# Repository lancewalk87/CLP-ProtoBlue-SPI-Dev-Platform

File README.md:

# ProtoBlue SPI Development Platform

### Project Structure:
* [**docs**](https://github.com/lancewalk87/CLP-ProtoBlue-SPI-Dev-Platform/tree/master/docs): Project Documentation.
* [**Drivers**](https://github.com/lancewalk87/CLP-ProtoBlue-SPI-Dev-Platform/tree/master/Drivers): Device System Software.
* [**Models**](https://github.com/lancewalk87/CLP-ProtoBlue-SPI-Dev-Platform/tree/master/Models): Device Hardware.
* [**PCBs**](https://github.com/lancewalk87/CLP-ProtoBlue-SPI-Dev-Platform/tree/master/PCBs): Device Circuits.
* [**Schematics**](https://github.com/lancewalk87/CLP-ProtoBlue-SPI-Dev-Platform/tree/master/Schematics): Device Schematics.  
* [**Client_Portals**](https://github.com/lancewalk87/CLP-ProtoBlue-SPI-Dev-Platform/tree/master/Client_Portals): Client Portals: Browser, Android, iOS, Windows, macOSX.    

General - General Purpose Digital Dev/Debug Platform
----------------------------------------------------
#### The ProtoBlue is capable of interfacing with any USB or Wifi/BlueTooth Enabled device, this allows for dynamic and convenient production testing via it's numerous onboard GPIO configurations and peripheral I/0. Capable of transceiving data of up to 72.2Mbps, the ESP8266EX Wireless chip offers a standard Wifi enabled (implementing TCP/IP as well as WLAN MAC protocols) baseband, clocked at 2.4GHz (Rx/Tx) making connection to the debugger ubiquitious amoungest all modern devices. In addition to efficent onboard power management (See Schematic Pg.3 - System Power Diagram), the device is capable of functioning independent of a sustained power supply and has an onboard 3.7v 560mAH LIPO battery complete with Temp Sense for safe and efficent battery rechargablity when the device is plugged in.

#### The Client Portal, available on iOS, Android, macOS, and Windows, acts as a fully functional MCU SDK, and Debug IDE. Allowing for both standard Assembly C/C++ binaries, as well as the Ardunio IDE (Objective-C) equivalent. The versataile operating system, and accessible GPIO makes the ProtoBlue the most reliable and efficent Debug platform available for any and all MCUs. In addition to the convinent ability to fix code reliably, the ProtoBlue Client Portal allows you to view (either post or pre debug session) individual bit states at any given device I/O Port, ADC, EEPROM, Interrupt, Clock, or SPI, you can investiga te each of your device's operations at a binary level.  

#### Given an additional 16GB of Non-Volataile NAND Flash Memory, you can store, edit, and review existing debug sessions in order to illustrate a more clear and foundational understanding of the intricate circuit you are trying to work the kinks out of. This storage also allows you to keep your projects together in a virtual space that is always connected to the hardware capable of performing real-world tests, without the tedious and redundant act of building new testing modules everytime you want to start or resume a different project.  

#### The ProtoBlue, as mentioned above, is capable of performing debug sessions without an additional MCU because the Primary MCU is not integral to the device's Power Management, USB, Wireless, or NAND Flash Memory functionality. Meaning the massive WS2812Bx48 Individually Addressable RGB LED Arrary can be used for a vast number of things ranging from validating data manipulative software (i.e. bitwise tests, timer tests, ttl comparisons), to the implementation of algorithms (i.e. Recursive, Backtracking, Divide/Conquer, Randomizing), to the optimization of the Device RunCycle (i.e. Multithreading, Preprocessing, Error/Exception Handling), to the efficent delegation of finite System resources (SRAM Deallocation/Allocation, Encryption/Overwriting of superfluous data, Conserving Energy by Shifting Power Modes). In conjunction to the LED Array, there are also Buttons connected to the Primary MCU, allowing for variable tactile user inputs.

### Architecture Support & Device Compatibility
#### The debug platform is capable of connecting to any device whose controller has ISP capabilities, this will include the vast majority of main line MCUs; including that of PIC series, and AVR series Microcontrollers. Depending on the MCU FlashROM made accessible to the ProtoBlue, the device will be capable of interfacing with the registers to grant access to the complex and detailed debuging tools defined above.

Debugging & Programming Targets
-------------------------------
### Programming Your Target
#### Make the proper ICSP connections to your target device's SPI (VCC, GND, MOSI, MISO, SCK, RESET), the ProtoBlue will interpret the target's signature and attempt to evaluate any preexisting EEPROM data. After configuring any neccesary ICSP variables, and cacheing a record of the debug session to it's NAND Flash Storage for later evaluation, the ProtoBlue will begin programming your target with the specefied code. You can review active or past debug sessions in the "debug" view of whatever client device you're using to carry out your tests (See Project Overview for full details on the Native Client environments).

### Debugging Your Target
#### Once your target has been uploaded with a binary, and is executing the instruction set accordingly you will be able to begin your debug session. After the ProtoBlue has completed programming over ISP, the user portal will give the option to begin a serial debug session. If you wish to proceed in debugging, select continue, and set the debug session settings when the window to do so presents itself.

#### These presets allows you to define the session's level of detail, certain types of debug sessions don't require massive amounts of detail, while others do, these presets allow you to determine that accuracy before the the initialization of the testing process. Once the session has been defined, the Protoblue will begin monitoring the target in a similar fashion to a typical JTag device.

#### When you have observed the behavior you either expected or did not expect, you can terminate the debug session and save it to your project cache.

### Bootloading Your Target
#### The onboard NANDFlash has allocated stoarge space to industry standard Bootloaders, the most prominent of which being the Ardunio Bootloader for AVR series Microcontrollers. For this example we will use this bootloader to demonstrate how to successfully bootload a target, though please note, you can upload any bootloader to your ProtoBlue and be successful in uploading it to a target.

#### To bootload a target you must connect the ProtoBlue via ISCP to your target's ICSP.

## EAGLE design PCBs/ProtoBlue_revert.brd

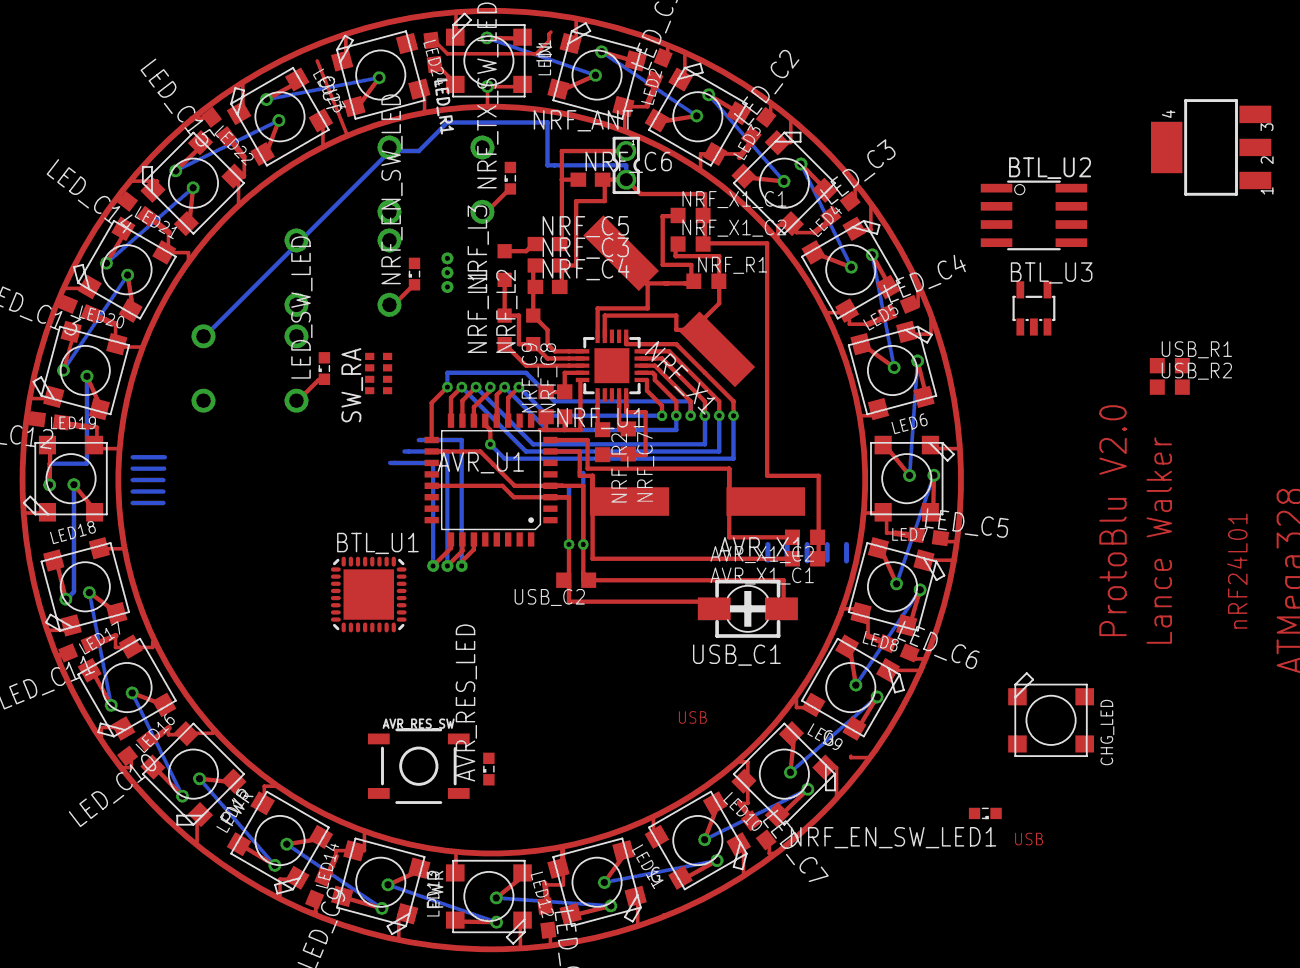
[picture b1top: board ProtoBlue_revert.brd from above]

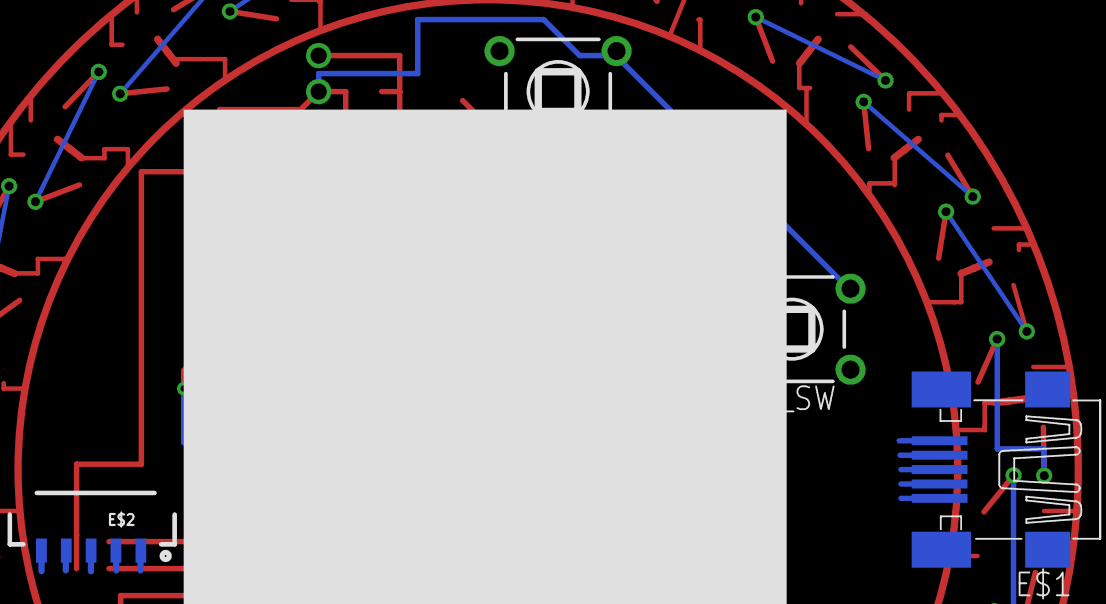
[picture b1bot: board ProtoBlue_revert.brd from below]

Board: 2 copper layers, 82 parts (5 on the bottom side), 3 nets.

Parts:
AVR_RES_LED: LED_SML0603
AVR_RES_SW: TACTILE_SWITCH_SMD_5.2MM
AVR_U1: 328AU; VQFP32
AVR_X1: 16MHz; CSM-7X-DU
AVR_X1_C1, AVR_X1_C2: 22pF; C0603K
BTL_IC1: MC33269ST-5.0T3; SOT223
BTL_U1: ATMEGA8U2-MU; QFN32
BTL_U2: SO08
BTL_U3: LP2985-33DBVR; SOT23-DBV
CHG_LED: WS2812B5050; WS2812B-NARROW
E$1: USB; 32005-400
E$2: BATT_IN; 1X05_1MM_RA
LED1, LED2, LED3, LED4, LED5, LED6, LED7, LED8, LED9, LED10, LED11, LED12, LED13, LED14, LED15, LED16, LED17, LED18, LED19, LED20, LED21, LED22, LED23, LED24: WS2812B5050; WS2812B-NARROW
LED_C1, LED_C2, LED_C3, LED_C4, LED_C5, LED_C6, LED_C7, LED_C8, LED_C9, LED_C10, LED_C11, LED_C12, LED_C13, LED_C14, LED_C15: 100nF; C0603
LED_R1: 0603-NO
LED_SW: TL1105T
LED_SW_LED: LED_SML0603
NRF_ANT: 332-02
NRF_C3: 2.2nF; C0603
NRF_C4: 4.7pF; C0603
NRF_C5: 1.5pF; C0603
NRF_C6: 1pF; C0603
NRF_C7: 33nF; C0603K
NRF_C8: 1nF; C0603K
NRF_C9: 10nF; C0603K
NRF_EN_SW: TL1105T
NRF_EN_SW_LED, NRF_EN_SW_LED1: LED_SML0603
NRF_L1: 8.2nH; L2012C
NRF_L2: 3.9nH; L2012C
NRF_L3: 2.7nH; L2012C
NRF_R1: 1M; C0603K
NRF_R2: 22K; C0603K
NRF_TX_SW: TL1105T
NRF_TX_SW_LED: LED_SML0603
NRF_U1: nRF24L01; QFN20
NRF_X1: 16MHz; CSM-7X-DU
NRF_X1_C1, NRF_X1_C2: 22pF; C0603K
SW_RA: 1K; 0603-ARC
USB_C1: 47uF; 3018_11
USB_C2: 100nF; C0603K
USB_R1, USB_R2: 100nF; C0603K

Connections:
GND: AVR_U1.3, AVR_U1.21, E$1.5, NRF_ANT.2
NRF_ADT1: NRF_L1.2, NRF_L2.1, NRF_L3.1
VCC: AVR_U1.4, AVR_U1.6, AVR_U1.18, E$1.1

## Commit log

2018-11-01 Create LICENSE
2018-11-05 v1.0.0
2018-11-05 v2.0.0
2019-01-27 v2.0.1
    Updated project details, documentation, and source.
2019-01-27 Readme Update
2019-01-27 v2.0.2

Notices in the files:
parts and their libraries:
microbuilder: This work is placed in the public domain, and may be freely used for commercial and non-commercial work with the following conditions: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
SparkFun-Switches: Licensing: Creative Commons ShareAlike 4.0 International - https://creativecommons.org/licenses/by-sa/4.0
